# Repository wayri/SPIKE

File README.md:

# SPIKE - Multiphysics Simulation Workbench

<p align="center"><strong>PCB-focused multiphysics, from board to complete assembly.</strong></p>

<p align="center">

</p>

SPIKE is an open-source, local-first workbench for power integrity (PI), signal
integrity (SI), circuits, thermal and airflow, selected EM/RF, and bounded
mechanical workflows. It keeps PCB, assembly, material, study, and result
evidence together for supported 2D and 3D workflows.

> [!WARNING]
> **0.4.0-alpha.1 is an experimental development preview. Knowledgeable human
> numerical and firmware review remains pending.** It is not a stable,
> qualified, safety-assured, or production engineering release. Publication
> does not qualify any method, model, package, or result. Read the
> [release notes](docs/releases/v0.4.0-alpha.1.md) and
> [solver evidence](docs/SOLVER_STATUS.md) before relying on an analysis.

## Contents

| Start here | Explore | Reference | Participate |
| --- | --- | --- | --- |
| [Download 0.4.0-alpha.1](#download-040-alpha1) | [Interface](#current-ui-and-navigation) | [Capabilities](#pcb-analysis-capabilities) | [Report an issue](https://github.com/wayri/SPIKE/issues) |
| [First workflow](#start-a-study) | [Analysis gallery](#analysis-gallery) | [Solver modules](#solver-modules-and-the-solver-suite) | [Contribute](CONTRIBUTING.md) |
| [ESP32 walkthrough](docs/ESP32_QUICKSTART.md) | [Examples](examples/README.md) | [CLI and documentation](#cli-and-documentation) | [Discord](https://discord.gg/UCmeR9ypzQ) |
| [Release notes](docs/releases/v0.4.0-alpha.1.md) | [Headroom and limits](#part-limits-and-operating-headroom) | [Extensions](#extensions) | [License](#license) |

## Download 0.4.0-alpha.1

Release candidate `4f550c0f` passed the four-platform CI run
[`39572252308`](https://github.com/wayri/SPIKE/actions/runs/39572252308).
Choose the asset for your platform and verify its adjacent SHA-256 file. Asset
availability and CI success are packaging evidence; neither establishes
numerical qualification or supported-platform acceptance.

| Platform | Experimental package | SHA-256 |
| --- | --- | --- |
| Windows x64 | [**Download EXE**](https://github.com/wayri/SPIKE/releases/download/v0.4.0-alpha.1/SPIKE_0.4.0-alpha.1_x64-setup.exe) | [checksum](https://github.com/wayri/SPIKE/releases/download/v0.4.0-alpha.1/SPIKE_0.4.0-alpha.1_x64-setup.exe.sha256) |
| Linux x86_64 | [**Download Flatpak**](https://github.com/wayri/SPIKE/releases/download/v0.4.0-alpha.1/SPIKE_0.4.0-alpha.1_linux-x86_64_EXPERIMENTAL.flatpak) | [checksum](https://github.com/wayri/SPIKE/releases/download/v0.4.0-alpha.1/SPIKE_0.4.0-alpha.1_linux-x86_64_EXPERIMENTAL.flatpak.sha256) |
| macOS Apple silicon | [**Download DMG**](https://github.com/wayri/SPIKE/releases/download/v0.4.0-alpha.1/SPIKE_0.4.0-alpha.1_macos-arm64_EXPERIMENTAL.dmg) | [checksum](https://github.com/wayri/SPIKE/releases/download/v0.4.0-alpha.1/SPIKE_0.4.0-alpha.1_macos-arm64_EXPERIMENTAL.dmg.sha256) |
| macOS Intel | [**Download DMG**](https://github.com/wayri/SPIKE/releases/download/v0.4.0-alpha.1/SPIKE_0.4.0-alpha.1_macos-x86_64_EXPERIMENTAL.dmg) | [checksum](https://github.com/wayri/SPIKE/releases/download/v0.4.0-alpha.1/SPIKE_0.4.0-alpha.1_macos-x86_64_EXPERIMENTAL.dmg.sha256) |

See [platform installation and CLI commands](docs/PLATFORM_PACKAGES.md). Older
Windows Gamma and 0.3.5 Linux/macOS packages are historical artifacts and do
not contain this candidate source.

## Start a study

| Step | In SPIKE | Check before continuing |
| ---: | --- | --- |
| 1 | Import a board or open a `.spike` project. | Read the import diagnostics; omitted objects and substituted 3D models remain explicit. |
| 2 | Choose a workspace or press **Ctrl+K** for an action. | Select the intended physics and solver route. Similar plots may come from different models. |
| 3 | Define nets, ports, materials, sources, loads, boundaries, and returns. | A footprint, geometry import, or prepared case does not supply missing engineering assumptions. |
| 4 | Review model status, mesh, units, and prerequisites, then run. | External engines require separate compatible installations. A failed or incomplete result never becomes a pass. |
| 5 | Inspect residuals, conservation checks, warnings, probes, and limits. | Plot appearance alone is not validation. Compare against an independent reference for the intended use. |
| 6 | Save the project and export a report with provenance. | Keep inputs, engine/source versions, diagnostics, and limitations with shared results. |

Fast entry points: [five-minute ESP32 walkthrough](docs/ESP32_QUICKSTART.md) ·
[UI quick start](docs/UI_QUICKSTART.md) · [task sequences](docs/USER_TASK_SEQUENCES.md) ·
[runnable examples](examples/README.md)

## Current UI and navigation

Clean mode keeps a global header plus document and assembly tabs. Open a domain
from **Workspaces**, choose **Menu > All actions**, or press **Ctrl+K**. Selecting
an object opens its properties; **Show hidden tools** restores closed panels.
The six menu sections are **Project**, **Design & view**, **Analyze**, **Results
& reports**, **Tools**, and **Help**. The [visual navigation guide](docs/UI_NAVIGATION.md)
maps section ownership, menu depth, keyboard navigation, and the import -> setup
-> mesh -> solve -> results -> save loop.

| Actual development UI, 19 October 2026 | Actual command search, 19 October 2026 |
| --- | --- |
|  |  |
| Imported geometry and component stand-ins; no analysis was executed. | Search suggestions only; no command or analysis was executed. |

These are actual local **browser development UI captures**, not mockups, solver
results, native desktop acceptance captures, or packaged application evidence.
They use the public ESP32 board recorded in the
[capture manifest](app/public/help/ui-current/manifest.json). Graphite/Light
workspace appearance and Graphite/Light/AMOLED viewport appearance are separate
preferences.

The main field viewport can display supplied cells, points, velocity arrows,
temperature and other scalar fields, connected supplied curves, and saved frame
playback. Sparse samples are not joined across unknown gaps. CFD previews without
cell dimensions remain point samples. Renderer-generated frozen-field paths are
approximate presentation, not transient particle paths. See
[field visualization](docs/FIELD_VISUALIZATION.md); the planned Blender adapter
is not implemented.

## Analysis gallery

The eight images below are **computed documentation plots from executed named
examples and postprocessors**. They are not UI screenshots, measurements, or
evidence that every model runs in every workspace. Follow the
[gallery audit and reproduction guide](docs/ANALYSIS_GALLERY.md) for inputs,
units, hashes, model status, and limitations.

| Area | Computed plot | Demonstrated boundary |
| --- | --- | --- |
| PI |  | Retained dielectric electroquasistatic admittance and power accounting; not a full-board DC map or full-wave solve. |
| SI |  | Supplied RLGC line response and coherent longitudinal quantities; no new geometry extraction or measured channel claim. |
| EM |  | Huygens postprocessing of synthetic boundary samples; not a newly executed Maxwell solve or absolute gain. |
| Thermal |  | Steady two-solid conduction with a matched contact; not package-calibrated board prediction. |
| Hybrid |  | Iterated DC loss and temperature feedback with explicit material law; not general simultaneous multiphysics. |
| CFD |  | Two-dimensional laminar lid-driven cavity reference; not enclosure airflow, turbulence, or CHT. |
| CHT |  | Bounded conjugate solid/fluid laminar channel; not a general enclosure solve. |
| Multiboard |  | Explicit reduced harness and thermal networks; not full spatial fields across all boards. |

## PCB analysis capabilities

| Area | Available workflow | Current limit |
| --- | --- | --- |
| Board and project | Import KiCad PCB data into `SpiDeR`; inspect 2D layers and assembled 3D; save versioned projects with study cases. | Some KiCad features or 3D models may be omitted or substituted. Review each import report. |
| Power integrity and circuits | Supported DC voltage-drop, harness, PEEC, PDN, power-tree, and circuit workflows with explicit sources, loads, returns, mesh, and limits. | Simplified conductor/return models apply. Converter behavior and pin mapping must be supplied. |
| Signal integrity | Loaded RLGC or Touchstone channels with explicit ports and terminations; S-parameters, reflection, TDR/TDT, eyes, and NEXT/FEXT where returned. | Port networks contain no spatial E/H fields. Nonlinear IBIS-AMI and protocol checks are not implemented in this route. |
| Thermal | Object-node, 2D board-plate, and layered steady/transient models; explicit powers, heat paths, and boundaries. | Cooling presets prescribe heat-transfer coefficients rather than solving airflow; board grids omit detailed package geometry and CHT. |
| Electromagnetics | EMerge antenna adapter plus separate openEMS and internal screening routes; display returned S-parameters, cuts, and sampled relative patterns. | The EMerge board export is a simplified two-layer, one-dielectric model. Normalized display radius/color is not absolute gain. |
| CFD and CHT | Experimental bounded native laminar references, retained-solid thermal routes, and separately admitted external adapters. | Isothermal airflow is not CHT. Reference cases do not qualify arbitrary enclosures, turbulence, or fan assemblies. |
| Hybrid and multiboard | Supported reduced electrothermal/scalar coupling and explicit board, connector, interconnect, and contact models. | Coupling is workflow-specific, not a general all-domain simultaneous solve. |
| Visualization and reports | 2D/3D result layers, returned-value probes, study comparison, and reports with units, settings, warnings, and status. | Only quantities returned by the selected analysis can be plotted or probed. |
| Automation | Local worker and CLI, extension/solver managers, and optional MCP bridge for supported project and study tools. | Local models need a separate runtime and a tool-capable model; MCP is limited to exposed SPIKE tools. |

### Part limits and operating headroom

[Part limits and stress](docs/PART_LIMITS.md) compares captured observations
against occurrence-specific declared voltage, current, temperature, power,
mechanical stress, and frequency allowances. It reports stress/headroom,
coverage, provenance, and pass/fail/incomplete states in JSON/CSV. Missing
evidence never becomes a pass. Temperature percentages require an explicit
reference such as ambient. These checks are declared-limit comparisons, not
automatic datasheet qualification, reliability, lifetime, fatigue, or combined
stress predictions.

### Circuit simulation choices

The circuit workspace has a built-in linear solver and separate
[ngspice](docs/SOLVER_STATUS.md) and SPIKES backend routes. Select an engine for
the supplied circuit model and check runtime availability. **SPIKES Studio is a
separate program and is not included in the SPIKE desktop release.** SPIKE uses
only its backend for supported structured runs. See the
[circuit workflow](docs/USER_TASK_SEQUENCES.md).

## Solver modules and the solver suite

Open **Solver manager** from **Ctrl+K** to inspect named modules, scope,
dependencies, runtime readiness, and the appropriate setup workflow.

| Module family | Named workflows | Scope |
| --- | --- | --- |
| PI | DC PI, 2.5D PI, PI Transient, 3D DC conduction, PDN and filters | Reduced networks, quasi-static PEEC, supported transients, bounded solid DC, and explicit circuits. |
| SI | Networks, channels, eye and protocol screens | Sampled networks, supported line/channel models, and deterministic screens. |
| Thermal and coupling | Board/solid thermal, assembly electrothermal, PWM electrothermal | Explicit heat models and mapped loss/temperature feedback. |
| CFD and CHT | 2D CFD, channel airflow, admitted external cooling/CHT adapters | Bounded native references and separately installed engines; isothermal CFD and CHT remain distinct. |
| EM and RF | 2D magnetic FEM, lumped EM machines, openEMS and EMerge adapters | Bounded magnetic models and supported external field workflows. |
| Circuits | Circuit MNA, adaptive transient, I/Q device models, SMPS stability | Supported structured routes; some authoring/execution lives in separate Studio or CLI tools. |
| Mechanics and MCAD | 3D structural, thermoelastic, geometry/FreeCAD adapters | Bounded static mechanics, same-mesh coupling, and geometry exchange. |
| Assemblies and execution | Harness/board adapters, scalar co-simulation, parallel workers | Explicit interconnect and coupling contracts; parallel jobs do not automatically couple physics. |

Implemented first-party code and adapters are bundled by default. Solver blocks
are logical dependency groups, not separately installable packages. Bulk
selection previews dependencies; it does not install, remove, or execute them.
Optional engines need their own compatible installation and admission. Bundled
code, runtime readiness, and numerical qualification remain separate states.

| Module guide | Purpose |
| --- | --- |
| [Solver suite](docs/SOLVER_SUITE.md) | Module families and workflow entry points |
| [Solver blocks](docs/SOLVER_BLOCKS.md) | Dependency groups and unresolved external engines |
| [Solver manager](docs/SOLVER_MANAGER.md) | Engine selection, registration, and readiness |
| [Solver status](docs/SOLVER_STATUS.md) | Authoritative implementation and validation status |
| [Extension SDK](extension_sdk/README.md) | Process isolation, permissions, result contracts, and examples |

## Extensions

<details>
<summary><strong>Extension catalog and boundaries</strong></summary>

| Extension | Capability | Dependency and limitation |
| --- | --- | --- |
| [openEMS Suite](extensions/openems_suite/README.md) | Explicit-port HF PI/SI preparation and execution; supported result import. | Separate openEMS/CSXCAD installation; one excited port per run; no DC PI or thermal coupling. |
| [EMerge Suite](extensions/emerge_suite/README.md) | Simplified selected-net S-parameters and relative radiation patterns. | Separate compatible runtime; selected copper, aligned ports, rectangular bounds, one dielectric, and surface PEC. |
| [ODB++ Import](docs/ODB_AND_HARNESS_EXTENSIONS.md) | Experimental board-job import with quality diagnostics. | Unsupported symbols, compositing, and panel repeats are reported; retain the source archive. |
| [Harness Engineering](docs/ODB_AND_HARNESS_EXTENSIONS.md) | JSON/CSV/TSV connection editing and assembly binding. | Does not import other harness database formats. |
| [MCAD Collaboration](docs/MCAD_EXPORT.md) | Preview and named STEP, FreeCAD, BREP, and metadata export. | Requires FreeCAD; geometry exchange only. |
| [PWM Converter Analysis](extensions/converter-analysis/spike-extension.json) | Readiness checks and versioned setup envelope. | No converter solve or efficiency/loss calculation. |
| [Net Inventory](extensions/net-inventory/spike-extension.json) | Example SDK net/conductor inventory. | No numerical analysis. |

External result format, source, unit, and bounds checks do not repeat an external
engine calculation. See the [extension analysis contract](docs/EXTENSION_ANALYSIS_API.md).

</details>

## CLI and documentation

```powershell
.\spike.cmd --help
.\spike.cmd --output-format text inspect board.kicad_pcb
.\spike.cmd --output result.json analyze-dc board.kicad_pcb `
  --net VCC `
  --source 10,10,F.Cu,5 `
  --load 50,20,F.Cu,1
```

| Need | Guide |
| --- | --- |
| Commands, saved requests, batches, and reports | [CLI reference](docs/CLI.md) |
| User workflows and tutorials | [Documentation index](docs/README.md) |
| Numerical implementation status and limits | [Solver status](docs/SOLVER_STATUS.md) |
| Mathematics, methods, and references | [Mathematics](docs/SOLVER_MATHEMATICS.md) · [handbook](docs/SOLVER_HANDBOOK.md) · [references](docs/SOLVER_REFERENCES.md) |
| LM Studio, Ollama, and MCP | [Local LLM and MCP](docs/LOCAL_LLM_MCP.md) |
| Build, architecture, and contribution | [Developer guide](docs/DEVELOPER_GUIDE.md) · [architecture](ARCHITECTURE.md) · [contributing](CONTRIBUTING.md) |

The product direction includes larger assemblies and coordinated cross-domain
studies. Coverage and execution scale depend on the selected workflow;
large-scale arbitrary-assembly simulation remains a development target, not a
blanket validated capability. See [product scope](docs/PRODUCT_SCOPE.md).

## Help improve SPIKE

Share reproducible comparisons, especially where SPIKE falls short. Include a
small publishable example, tool versions, settings, geometry, materials, ports,
boundary conditions, and the observed difference. Review reports before sharing
board data. [Open an issue](https://github.com/wayri/SPIKE/issues) or join the
[Discord community](https://discord.gg/UCmeR9ypzQ); the invite opens in the
read-only welcome channel.

<details>
<summary><strong>Disclaimer and development disclosure</strong></summary>

SPIKE is a work in progress and is provided **AS IS**, without warranty or
guarantee of any kind, including accuracy, reliability, or fitness for a
particular purpose. Use it at your own risk. To the extent permitted by
applicable law, and unless otherwise agreed in writing, Yawar B (wayri) and the
contributors are not liable for any damage, loss, or other consequences arising
from using or being unable to use SPIKE, including incorrect results, design
errors, equipment damage, data loss, or financial loss. You are responsible for
checking inputs, assumptions, and results before relying on them. This summarizes
the warranty and liability provisions in the [Apache License 2.0](LICENSE); the
license terms govern.

SPIKE's development effort is largely LLM-driven under human review. Human
direction and responsibility remain distinct from LLM-generated proposals,
code, tests, and documentation. Passing tests and generated reports are
engineering evidence, not independent physical validation. Read the
[LLM-driven development disclosure](docs/LLM_DEVELOPMENT.md). This early
community preview may contain instabilities, bugs, and incomplete behavior.

</details>

## License

Copyright 2026 Yawar B (wayri) and SPIKE contributors. SPIKE-owned code and
documentation are licensed under [Apache 2.0](LICENSE), except where a file or
directory specifies different terms. Dependencies, external engines, and
example boards retain their own licenses; see
[third-party notices](THIRD_PARTY_NOTICES.md).

<details>
<summary><strong>Acknowledgements</strong></summary>

- Large language models have produced substantial proposals, code, tests, and
  documentation under human direction and review. The
  [development disclosure](docs/LLM_DEVELOPMENT.md) records this contribution
  and its limits.
- The KiCad project and its contributors for the PCB ecosystem SPIKE works with.
- The Tauri, React, Three.js, Plotly.js, and Lucide projects behind the desktop
  interface and plots.
- NumPy, SciPy, Shapely/GEOS, PyVista, wxPython, nanobind, Matplotlib,
  mplcursors, ReportLab, Apache Arrow, jsonschema, and Eigen contributors.
- [ngspice](https://ngspice.sourceforge.io/) contributors for the optional
  circuit engine.
- [openEMS](https://openems.de/) and
  [CSXCAD](https://github.com/thliebig/CSXCAD) contributors for the optional EM
  solver and geometry tools.
- Robert Fennis and [EMerge](https://github.com/FennisRobert/EMerge)
  contributors for the optional EM solver used in the ESP32 antenna example.
- The [OpenFOAM](https://www.openfoam.com/) community for the optional airflow
  solver, and the [FreeCAD](https://www.freecad.org/) community for the optional
  mechanical CAD integration.
- Berkeley Lab and the Regents of the University of California for the Marble
  reference board, and uysan for the open `iot-esp-eth` ESP32 example board.
- Contributors, testers, issue reporters, and documentation authors.

If a credit is missing, open an issue or pull request. Source and license details
for included examples and integrations are in
[third-party notices](THIRD_PARTY_NOTICES.md).

</details>

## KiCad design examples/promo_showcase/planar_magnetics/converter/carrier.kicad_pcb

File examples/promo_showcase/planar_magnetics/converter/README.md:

# 48 V → 1.8 V / 50 W planar-converter study

This is a complete editable **topology and routed geometry study**, plus an executed native Studio ideal-converter example. It is **not a fabrication-ready or current-qualified 50 W converter**. Power semiconductors, gate drivers, protection, insulation, component ratings, copper temperature rise and connector sharing remain unqualified. No hardware energization or release is authorized by the supplied files.

## Native files

- Open `carrier.kicad_pro` in KiCad 10.0.6; matching schematic and board plus local `Carrier.kicad_sym`, `Carrier.pretty`, symbol/footprint tables are included.
- The native schematic contains the full four-MOS primary bridge, 34-pin transformer module, four-MOS synchronous secondary bridge, output L/C, input/output and external G/S driver connectors. All MOS symbols and footprints are explicitly generic placeholders.
- Board: 100 × 90 mm, module origin (50,45) mm, 32.5 × 21.1 mm internal cutout for the protruding lower core, documentary 52 × 52 mm component-envelope border. The component border is not an enforced clearance/insulation rule.
- Every one of the 81 native required pad connections was routed across the two copper layers. All traces are 0.5 mm wide **geometric examples, not rated for the 27.8 A load**. Native DRC, unconnected count and schematic parity are each zero. No finding was excluded to achieve that result. Native reports retain the installed KiCad default ignored-check list.
- T1 local model is `${KIPRJMOD}/models/planar_transformer_assembly.step`. It contains the original 225-solid full module with two core halves, actual winding-board bodies/copper and 34 original pin solids; stock third-party header models are omitted. Native KiCad STEP export of the carrier with this model contains 226 manifold solid records (225 model solids + carrier body). Other carrier parts do not have 3D models and are not silently replaced with invented detailed packages.

T1 pin contract, relative to module origin in PCB mm:

| Terminals | Pads and positions | Net / polarity |
| --- | --- | --- |
| Primary | 1 at (-20,-1.27), 2 at (-20,+1.27) | PRI_A / PRI_B; dot P1 |
| Secondary S1 | 3..18: eight x positions -8.89,-6.35,-3.81,-1.27,+1.27,+3.81,+6.35,+8.89; rows y=20,22.54 | SEC_A; undotted |
| Secondary S2 | 19..34: same x positions, rows y=-20,-22.54 | SEC_B; dotted |

Primary P1 positive corresponds to secondary S2 positive under the companion winding orientation. The schematic dots and simulation `sec_b`/`sec_a` mapping preserve that sign. Symmetric rectification does not make the sign convention optional for other uses. Berg/header pin geometry is not a rating: 16 parallel contacts per secondary bank do not establish balanced sharing or safe total current. J3/J4 are original 5.08 mm external-driver G/S test-pad grids, not sourced Berg connector footprints.

## Run the native Studio example

In SPIKE Studio, **File > Open `converter.spksch`**; choose the owned native engine `app/src-tauri/resources/worker/spike-worker/_internal/spikes/spikes_c_api.dll` from this repository. The sibling circuit-worker DLL lacks the needed dependent-source ABI in this installation. The project retains graphical routes, voltage/current probes, three scopes and a **backward Euler** run profile. Run transient, inspect V(out), I(Lout), V(pri), and switch to Dashboard Run mode for the recorded scopes. No UI execution or recording is claimed by this package task.

Reproduce from repository root:

```powershell
.venv/Scripts/python.exe examples/promo_showcase/planar_magnetics/converter/run_converter.py
```

Matching `converter-base.cir` and `converter-refined.cir` are supported native netlists. Raw actual results and checks are under `output/promo-planar-magnetics-20261023/converter/`. The saved Studio project uses the refined 50 ns request and was reopened/source-checked through the native document API.

| Executed step | Mean output | Mean load current | Load power | Output ripple peak-to-peak |
| --- | --- | --- | --- | --- |
| 100 ns | 1.799921 V | 27.77655 A | 49.99564 W | 6.64851 mV |
| 50 ns | 1.800051 V | 27.77857 A | 50.00289 W | 6.70607 mV |

Statistics use time-weighted integration of the final 0.2 ms of a 1 ms run. Step halving changes mean voltage by 0.131 mV and ripple by 0.86%; both explicit acceptance checks pass. This is one bounded load case, not general convergence or controller stability qualification.

## Governing model and power audit

The existing owned native MNA engine solves all electrical states. Native K-coupled inductors are unsupported, so the model explicitly uses a power-conserving ideal transformer: `v_s=n v_p`, `i_p=-n i_s`, n=1/8, implemented using the supported E/F sources. Thus `v_p i_p+v_s i_s=0` independently of loading. Linear primary Lmag is 364.8 µH = 5700 nH × 8². The 5700 nH AL and ±25% small-signal tolerance are supplied core-candidate properties, **not a nonlinear/hot operating inductance or a FEM-derived value**; only the nominal value is exercised here.

The primary bridge is a **prescribed balanced bipolar ±48 V PWM voltage**, 100 kHz full cycle. The ideal synchronous bridge uses supported behavioral source pairs: `v_rect=m(t) v_s`, `i_s=-m(t) i_rect`, with prescribed m=+1/-1 during the respective polarity and m=0 in zero-voltage freewheel intervals. This conserves instantaneous port power, including ideal zero-voltage freewheel. It is not a four-device switch/diode commutation solution. A discrete smooth-switch candidate failed the native Newton solver; it was not presented as a completed result.

Nominal effective active duty is 0.3060620437, tuned for the named load and explicit edge timing. The 64.8 mΩ load follows R=1.8²/50; output is a CPU-like resistive load, not a CPU model. This is **fixed duty, not a feedback-regulated converter**, and does not establish load-step/line-step/startup protection behavior.

Supplied assumptions: primary series resistance 50 mΩ, output L=1 µH with 1 mΩ DCR, C=1000 µF with zero ESR, 1 GΩ secondary reference aid. Secondary copper, switch losses, capacitor ESR/ESL, leakage inductance, parasitic capacitance, deadtime/body diodes, switching loss and core loss are omitted. Do not infer efficiency, a device thermal load or hardware output ripple from the simplified values.

At 50 ns, transformer and ideal-rectifier instantaneous power residuals are each below 1.14e-13 W. An independently reduced backward-Euler energy identity uses right-endpoint source/resistor work, changes in `L i²/2` and `C v²/2`, and numerical dissipation `Σ[L(Δi)²+C(Δv)²]/2`. Residual is 1.18e-17 J over the audit window. Numerical dissipation is reported separately (0.2313 W at 50 ns versus 0.4706 W at 100 ns); it must not be called physical switching or core loss. Simple trapezoid power averages consequently do not close to the resistor sum.

## Physical schematic versus simulation

| Carrier item | Simulated counterpart / deliberate gap |
| --- | --- |
| Q1..Q4 and external J3 driver | Prescribed bipolar source; no actual primary MOSFETs or gate driver solved |
| Q5..Q8 and external J4 driver | Ideal power-conserving rectifier/freewheel source pair; no device commutation solved |
| T1 assembly | Nominal 8:1 ideal transform plus supplied linear Lmag, not solved N97 saturation/loss/thermal |
| L1/C2 | Specified ideal L/C and assumed DCR; placeholders lack sourced ratings, ESR and saturation data |
| C1 input decoupling | Value remains TBD; no DC-link capacitor/bridge-bus dynamics in the ideal source model |
| J2 output and CPU-like load | External 64.8 mΩ resistor; no CPU/package/VRM transient model |

## Native rebuild and evidence

Use installed KiCad Python for `build_carrier.py` followed by `route_carrier.py`, then run native schematic ERC and PCB DRC with schematic parity. The generator recreates the candidate files; do not use it over subsequent hand edits. The local source is firstparty Apache-2.0; the assembly STEP is original geometric demonstration material, and does not redistribute an official TDK CAD model. Core dimensions/material names originate in the separate core study evidence; retain that evidence with a shared pack. See LICENSE, NOTICE and source-provenance.json.

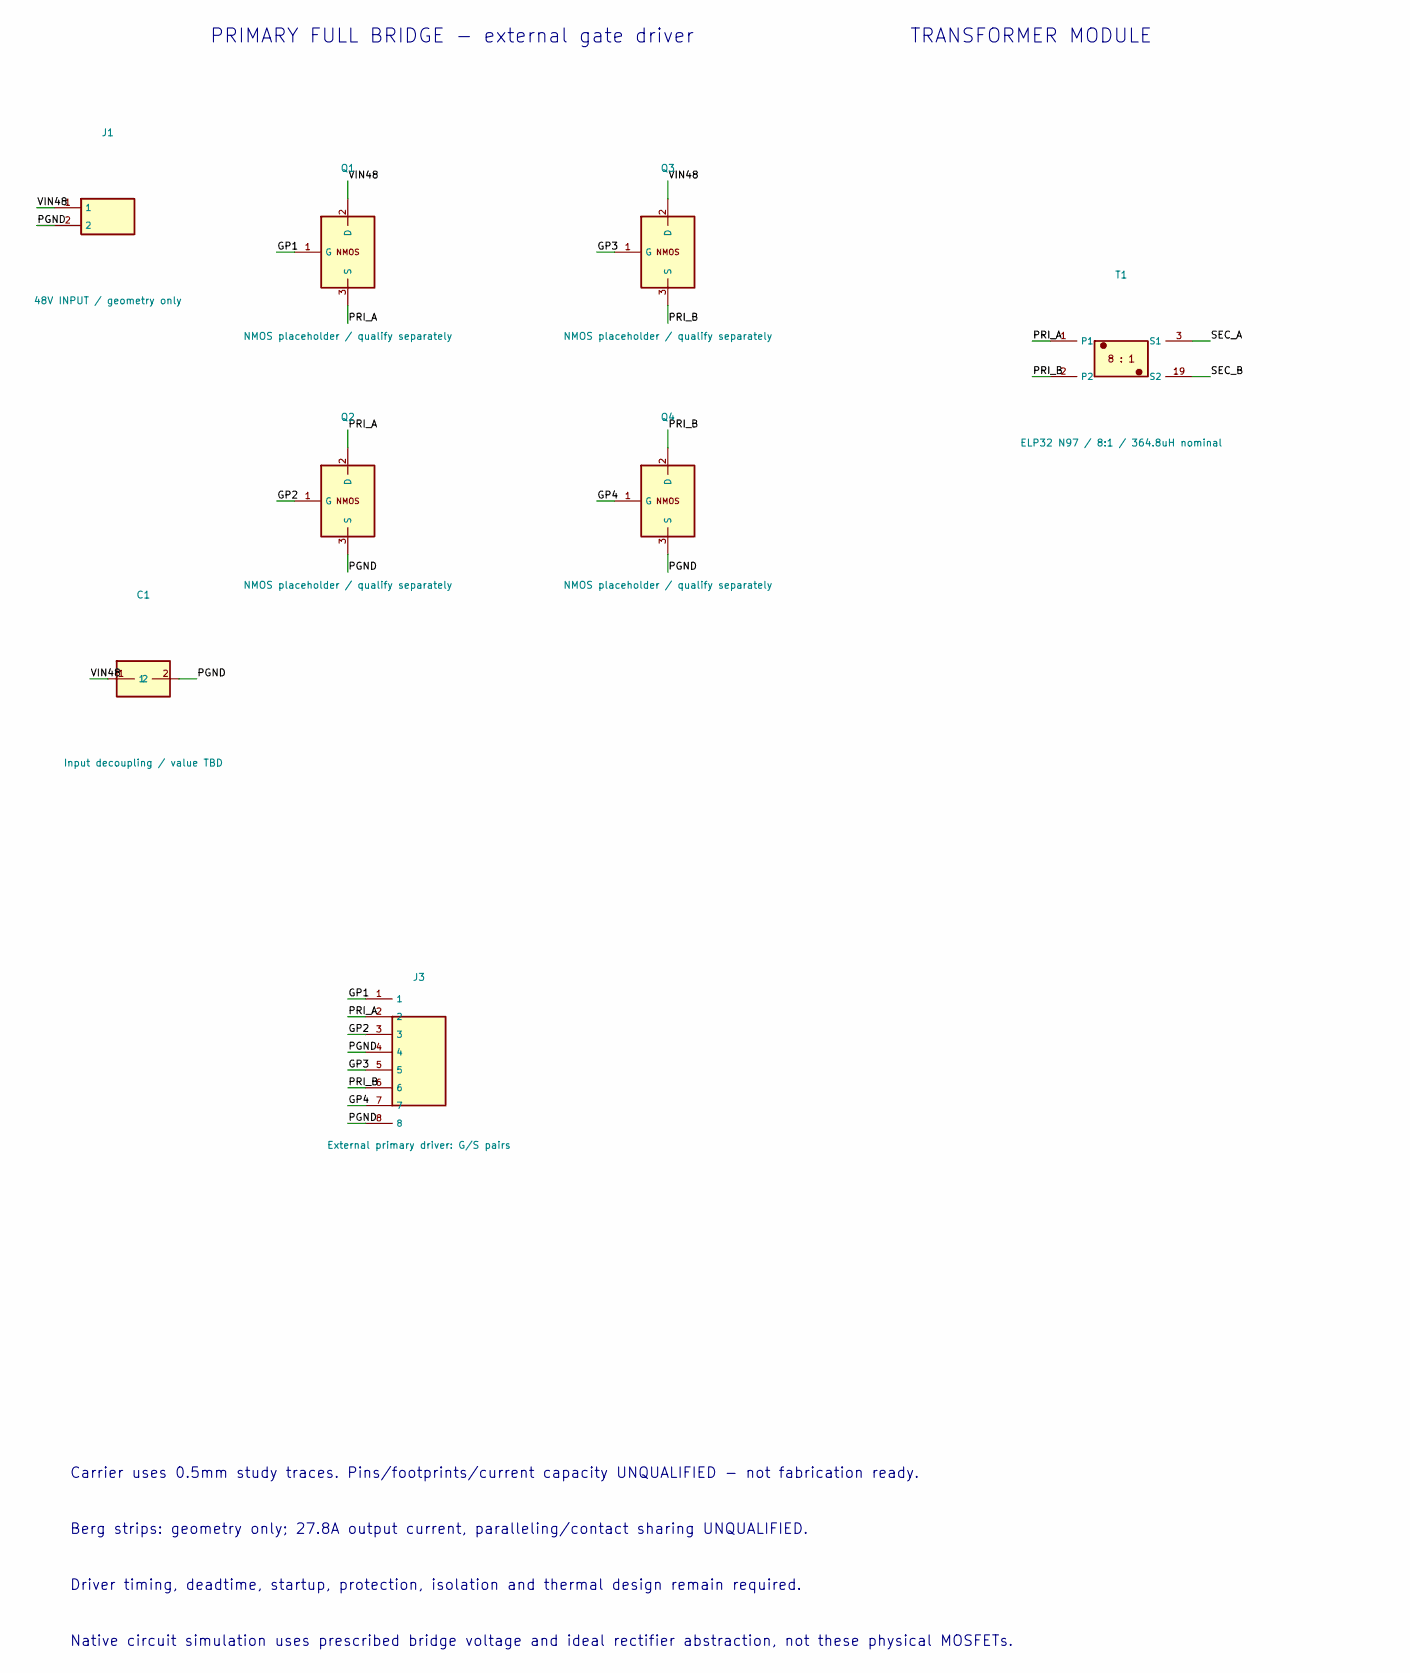
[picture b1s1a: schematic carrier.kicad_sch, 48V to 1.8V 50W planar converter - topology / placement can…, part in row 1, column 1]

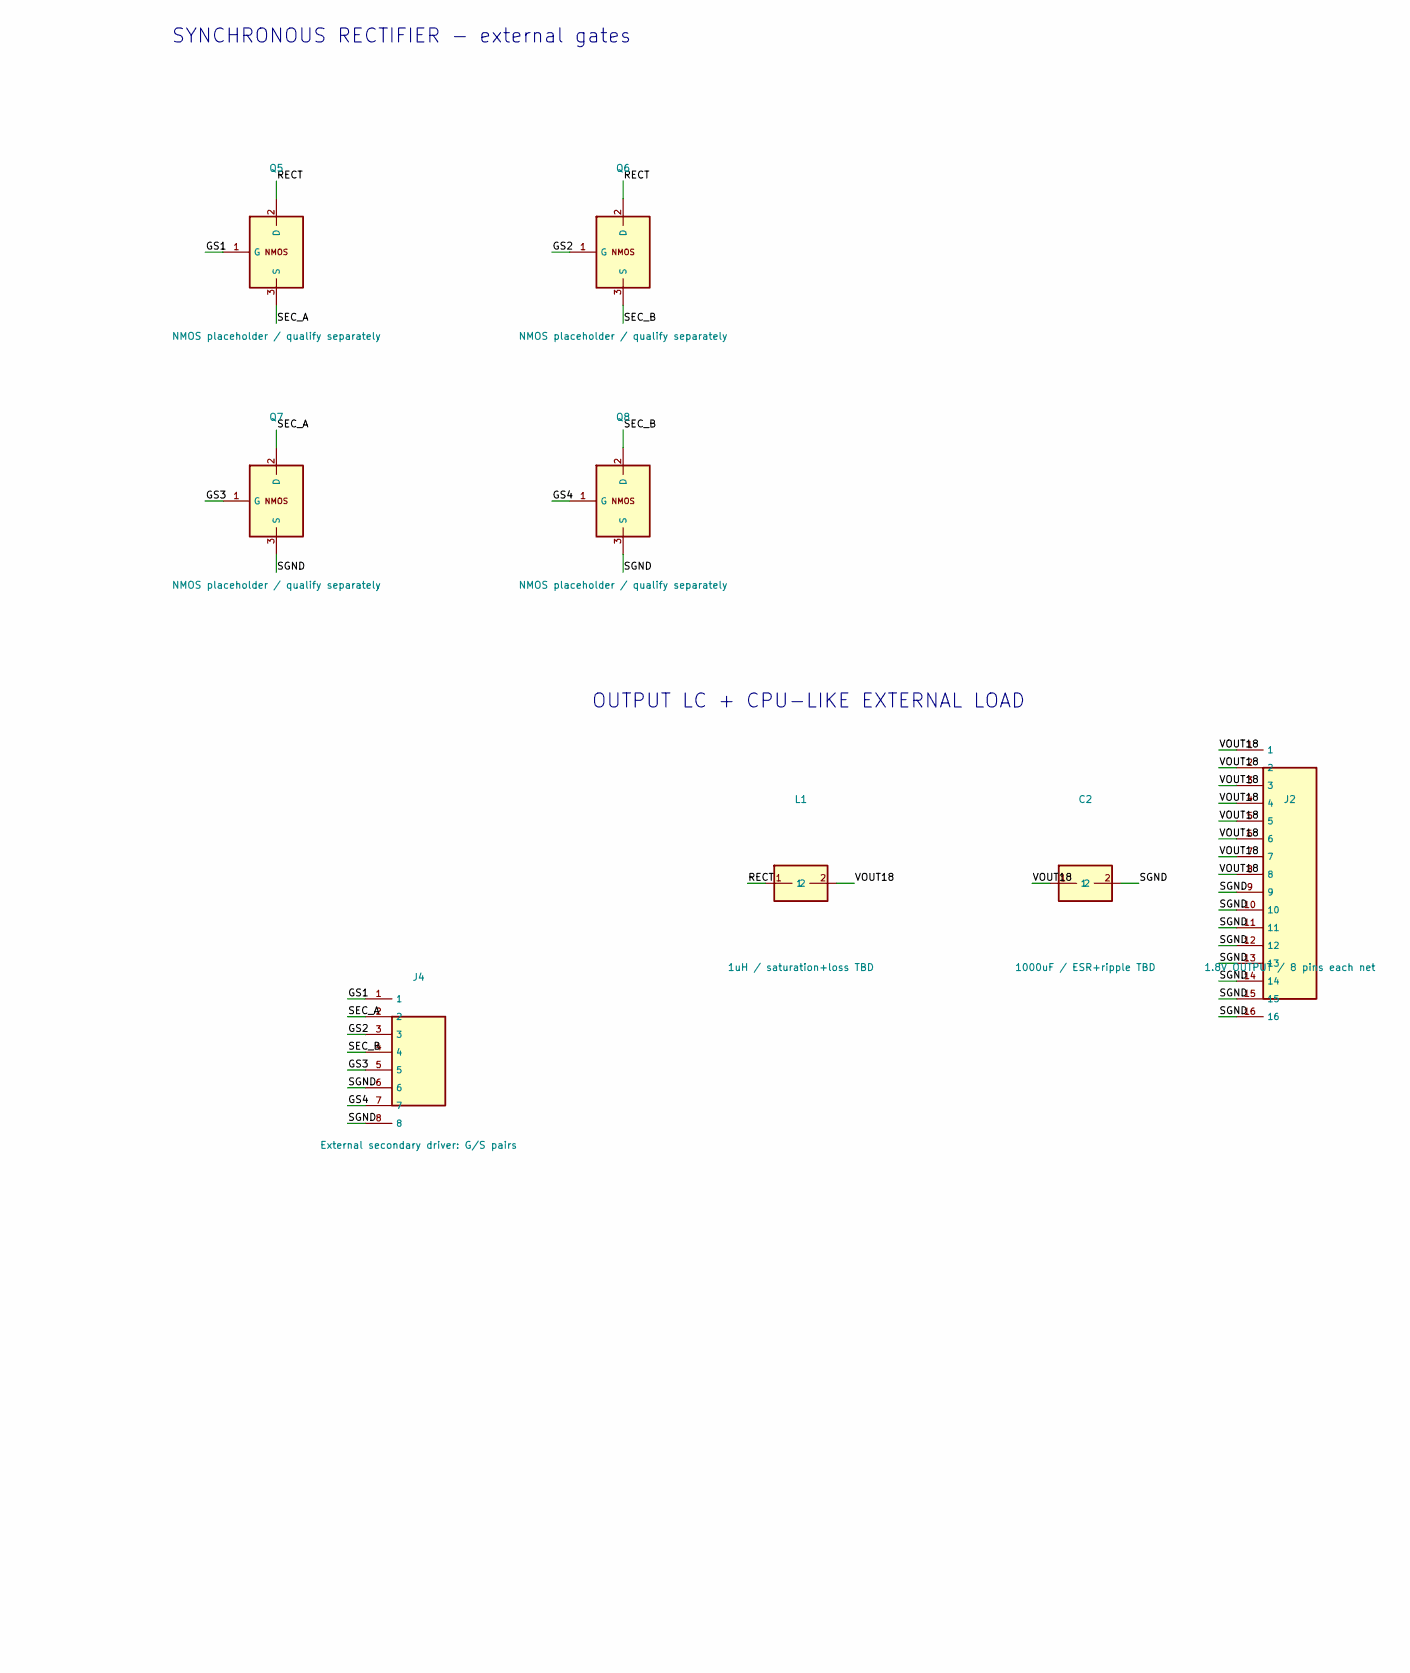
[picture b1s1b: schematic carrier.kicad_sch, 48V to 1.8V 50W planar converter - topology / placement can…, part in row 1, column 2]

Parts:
C1: Input decoupling / value TBD; Passive2_GeometryOnly
C2: 1000uF / ESR+ripple TBD; Passive2_GeometryOnly
J1: 48V INPUT / geometry only; Header1x2
J2: 1.8V OUTPUT / 8 pins each net; Header2x8
J3: External primary driver: G/S pairs; GatePads2x4_P5
J4: External secondary driver: G/S pairs; GatePads2x4_P5
L1: 1uH / saturation+loss TBD; Inductor_GeometryOnly
Q1, Q2, Q3, Q4, Q5, Q6, Q7, Q8: NMOS placeholder / qualify separately; MOS_GDS_GeometryOnly
T1: ELP32 N97 / 8:1 / 364.8uH nominal; PlanarTransformer_Module

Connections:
/GP1: J3.1, Q1.1 (G)
/GP2: J3.3, Q2.1 (G)
/GP3: J3.5, Q3.1 (G)
/GP4: J3.7, Q4.1 (G)
/GS1: J4.1, Q5.1 (G)
/GS2: J4.3, Q6.1 (G)
/GS3: J4.5, Q7.1 (G)
/GS4: J4.7, Q8.1 (G)
/PGND: C1.2, J1.2, J3.4, J3.8, Q2.3 (S), Q4.3 (S)
/PRI_A: J3.2, Q1.3 (S), Q2.2 (D), T1.1
/PRI_B: J3.6, Q3.3 (S), Q4.2 (D), T1.2
/RECT: L1.1, Q5.2 (D), Q6.2 (D)
/SEC_A: J4.2, Q5.3 (S), Q7.2 (D), T1.3 (S1), T1.4, T1.5, T1.6, T1.7, T1.8, T1.9, T1.10, T1.11, T1.12, T1.13, T1.14, T1.15, T1.16, T1.17, T1.18
/SEC_B: J4.4, Q6.3 (S), Q8.2 (D), T1.19 (S2), T1.20, T1.21, T1.22, T1.23, T1.24, T1.25, T1.26, T1.27, T1.28, T1.29, T1.30, T1.31, T1.32, T1.33, T1.34
/SGND: C2.2, J2.9, J2.10, J2.11, J2.12, J2.13, J2.14, J2.15, J2.16, J4.6, J4.8, Q7.3 (S), Q8.3 (S)
/VIN48: C1.1, J1.1, Q1.2 (D), Q3.2 (D)
/VOUT18: C2.1, J2.1, J2.2, J2.3, J2.4, J2.5, J2.6, J2.7, J2.8, L1.2

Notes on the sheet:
PRIMARY FULL BRIDGE - external gate driver
TRANSFORMER MODULE
SYNCHRONOUS RECTIFIER - external gates
OUTPUT LC + CPU-LIKE EXTERNAL LOAD
Carrier uses 0.5mm study traces. Pins/footprints/current capacity UNQUALIFIED - not fabrication ready.
Berg strips: geometry only; 27.8A output current, paralleling/contact sharing UNQUALIFIED.
Driver timing, deadtime, startup, protection, isolation and thermal design remain required.
Native circuit simulation uses prescribed bridge voltage and ideal rectifier abstraction, not these physical MOSFETs.

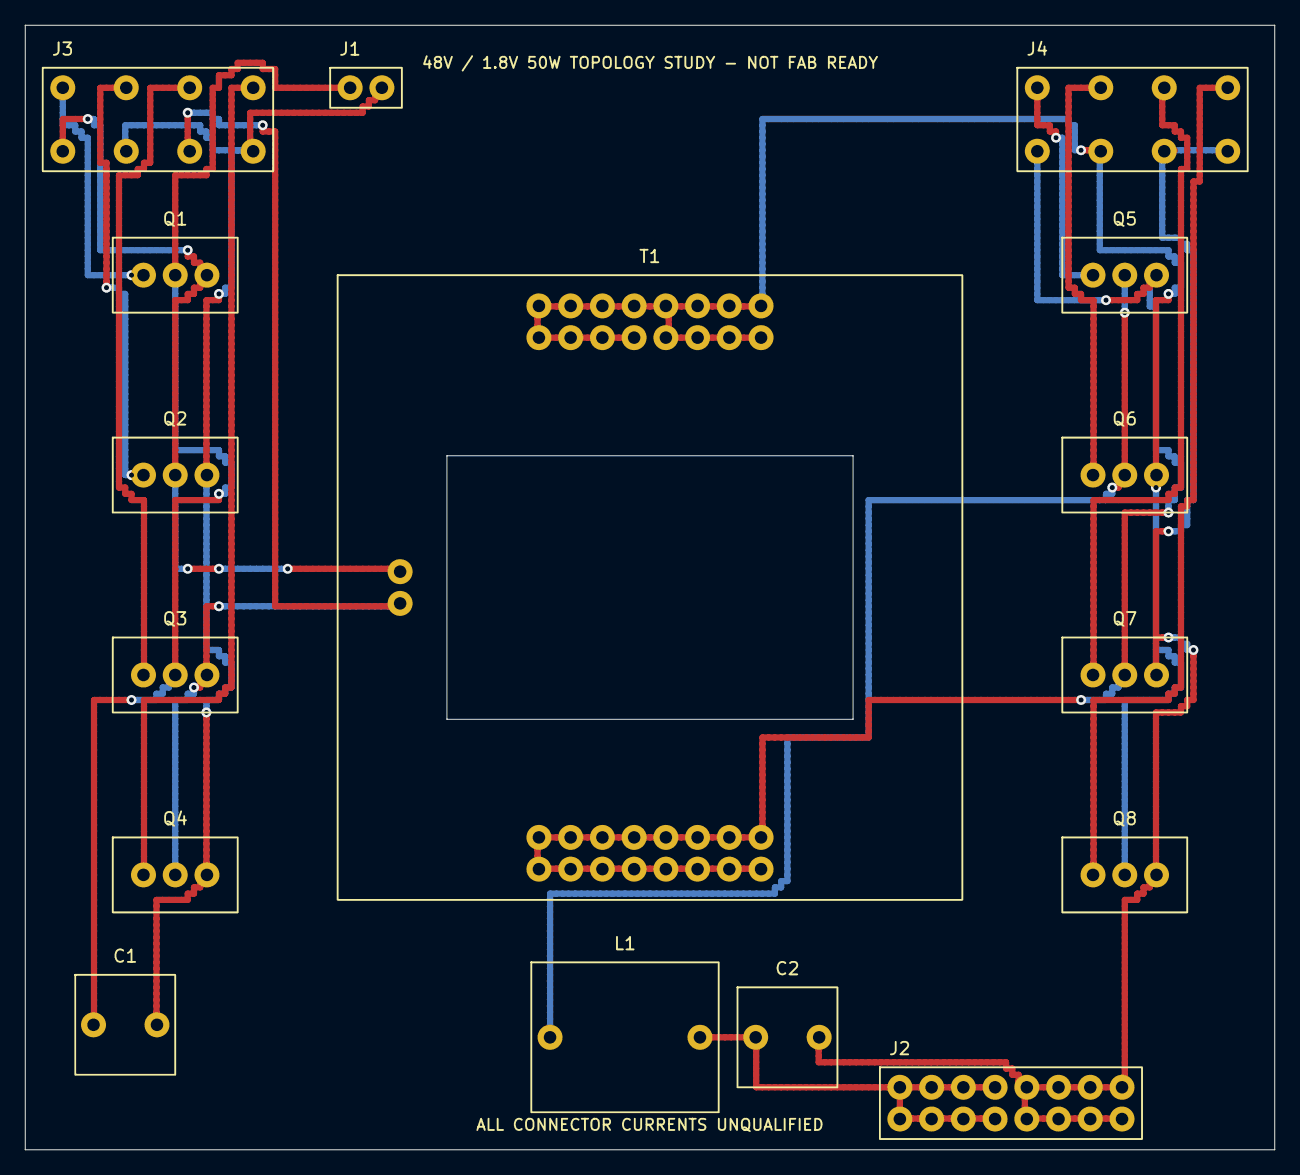
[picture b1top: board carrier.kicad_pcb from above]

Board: 2 copper layers, 100.0 x 90.0 mm, 16 parts (0 on the bottom side), 17 nets.
